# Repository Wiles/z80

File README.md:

# z80

## Purpose

Back in collage we had a real time operating systems course with targetted the Motorola 68000 CPU. It was a great course but our target platform was an emulator and not real hardware. This left a gap in my knoweldge of how things like chip selection and peripherals were handled by the hardware. Therefore I decided to design and build a barebones 8-bit computer and this is the results.

## Memory Map

| Start | End | Description |
| --- | --- | --- |
| 0x0000 | 0x7FFF | ROM |
| 0x8000 | 0x0000 | RAM |

## IO Map

| Start | End | Description |
| --- | --- | --- |
| 0x80 | 0x87 | UART |

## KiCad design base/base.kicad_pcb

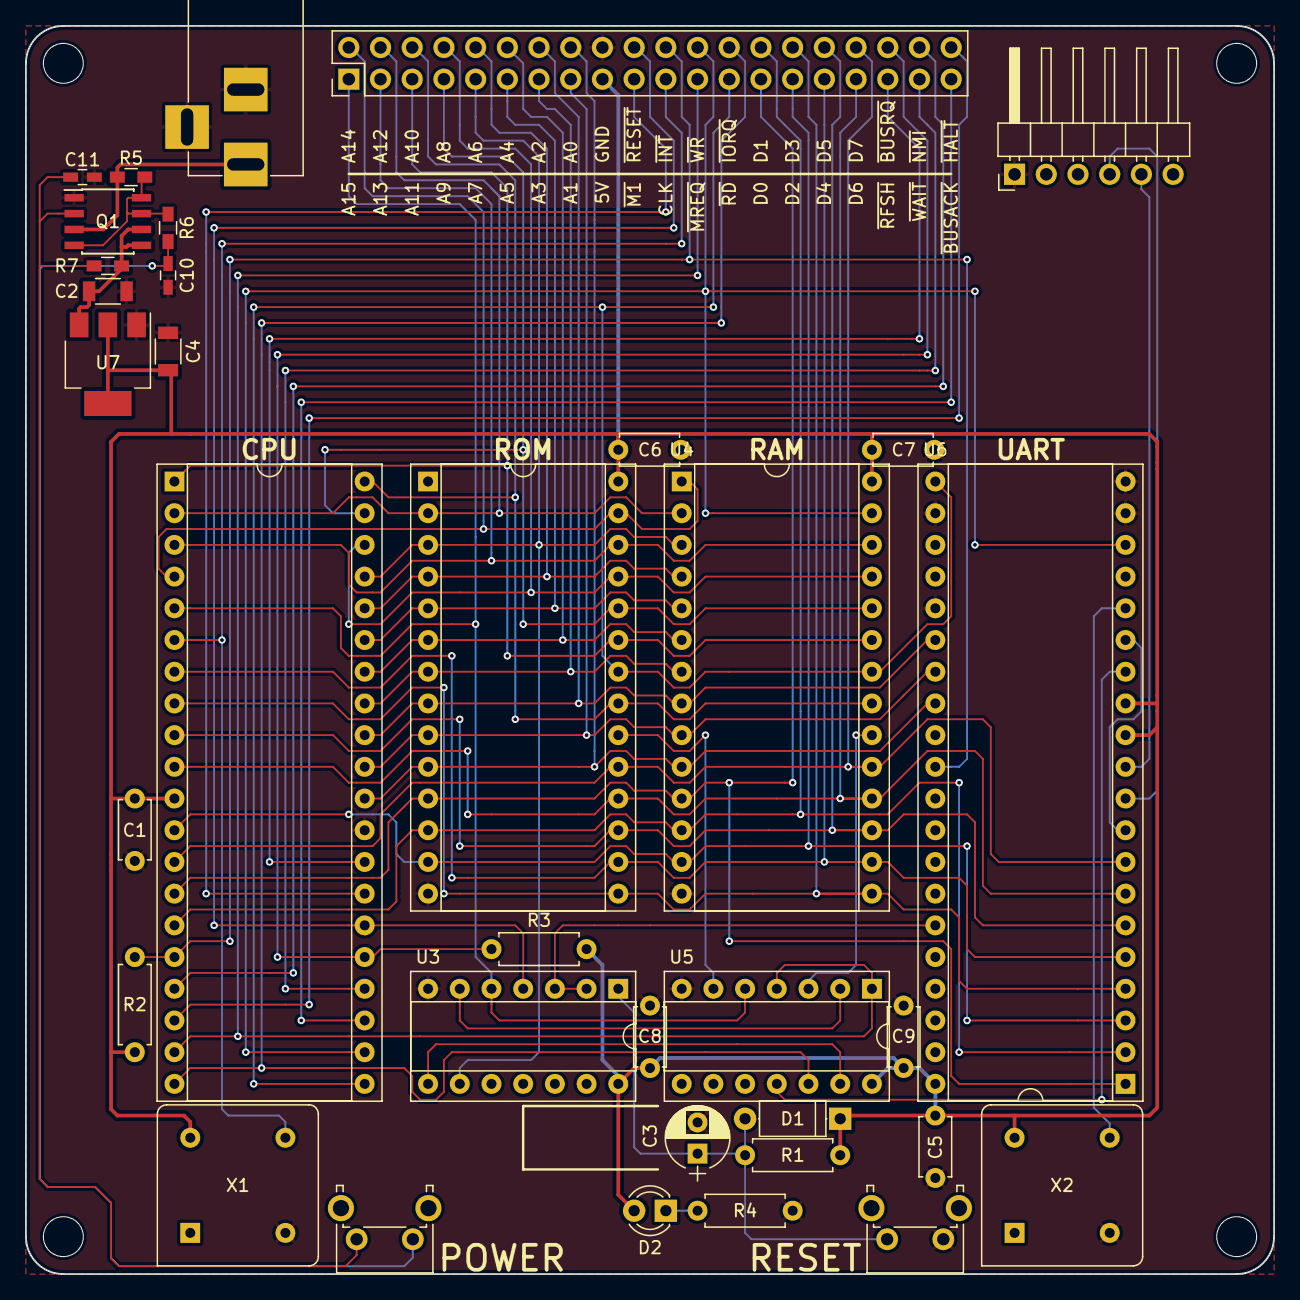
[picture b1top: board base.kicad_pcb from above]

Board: 2 copper layers, 100.0 x 100.0 mm, 35 parts (0 on the bottom side), 57 nets.

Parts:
C1, C5, C6, C7, C8, C9: .1 uF; C_Disc_D4.7mm_W2.5mm_P5.00mm
C2, C4: 10 uF; C_1206
C3: 47 uF; CP_Radial_D5.0mm_P2.50mm
C10: 1 uF; C_0603_HandSoldering
C11: .1 uF; C_0603_HandSoldering
D1: 1N4148; D_A-405_P7.62mm_Horizontal
D2: LED; LED_D3.0mm
J1: FTDI; Pin_Header_Angled_1x06_Pitch2.54mm
J2: Barrel_Jack; BARREL_JACK
J3: CONN_01X40; Pin_Header_Straight_2x20_Pitch2.54mm
Q1: IRF7309IPBF; SOIC-8_3.9x4.9mm_Pitch1.27mm
R1, R2, R3: 10k; R_Axial_DIN0207_L6.3mm_D2.5mm_P7.62mm_Horizontal
R4: 1k; R_Axial_DIN0207_L6.3mm_D2.5mm_P7.62mm_Horizontal
R5, R7: 10k; R_0603_HandSoldering
R6: 100k; R_0603_HandSoldering
SW1: RESET; SW_Tactile_SPST_Angled_PTS645Vx31-2LFS
SW2: POWER; SW_Tactile_SPST_Angled_PTS645Vx31-2LFS
U1: Z80CPU; DIP-40_W15.24mm_Socket
U2: 27C256; DIP-28_W15.24mm_Socket
U3: 7404; DIP-14_W7.62mm_Socket
U4: 55257; DIP-28_W15.24mm_Socket
U5: 7432; DIP-14_W7.62mm_Socket
U6: 16550; DIP-40_W15.24mm_Socket
U7: AP1117-50; SOT-223-3Lead_TabPin2
X1: 4 MHz; Oscillator_DIP-8
X2: 1.8432 MHz; Oscillator_DIP-8

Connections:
+5V: C1.1, C4.1, C5.1, C6.1, C7.1, C8.1, C9.1, D1.1, D2.2, J3.17, R1.1, R2.2, R3.2, U1.11, U2.28, U3.14, U4.28, U5.14, U6.12, U6.13, U6.40, U7.2, X1.8, X2.8
+VDC: J2.1, Q1.3, R5.2
+VSW: C2.1, Q1.5, Q1.6, R7.1, U7.3
/A0: J3.16, U1.30, U2.10, U4.10, U6.28
/A1: J3.15, U1.31, U2.9, U4.9, U6.27
/A2: J3.14, U1.32, U2.8, U4.8, U6.26
/A3: J3.13, U1.33, U2.7, U4.7
/A4: J3.12, U1.34, U2.6, U4.6
/A5: J3.11, U1.35, U2.5, U4.5
/A6: J3.10, U1.36, U2.4, U4.4
/A7: J3.9, U1.37, U2.3, U3.9, U4.3
/A8: J3.8, U1.38, U2.25, U4.25
/A9: J3.7, U1.39, U2.24, U4.24
/A10: J3.6, U1.40, U2.21, U4.21
/A11: J3.5, U1.1, U2.23, U4.23
/A12: J3.4, U1.2, U2.2, U4.2
/A13: J3.3, U1.3, U2.26, U4.26
/A14: J3.2, U1.4, U2.27, U4.1
/A15: J3.1, U1.5, U3.5, U5.5
/D0: J3.27, U1.14, U2.11, U4.11, U6.1
/D1: J3.28, U1.15, U2.12, U4.12, U6.2
/D2: J3.29, U1.12, U2.13, U4.13, U6.3
/D3: J3.30, U1.8, U2.15, U4.15, U6.4
/D4: J3.31, U1.7, U2.16, U4.16, U6.5
/D5: J3.32, U1.9, U2.17, U4.17, U6.6
/D6: J3.33, U1.10, U2.18, U4.18, U6.7
/D7: J3.34, U1.13, U2.19, U4.19, U6.8
BUSACK: J3.39, U1.23
BUSRQ: J3.36, R3.1, U1.25
CLOCK: J3.21, U1.6, X1.5
GND: C1.2, C2.2, C3.2, C4.2, C5.2, C6.2, C7.2, C8.2, C9.2, C10.2, C11.2, J1.1, J2.2, J2.3, J3.18, Q1.1, R4.1, SW1.1, U1.29, U2.14, U3.7, U4.14, U5.7, U6.19, U6.20, U6.22, U6.25, U7.1, X1.4, X2.4
HALT: J3.40, U1.18
INT: J3.22, R2.1, U1.16, U6.30
IORQ: J3.26, U1.20, U5.12
M1: J3.19, U1.27
MREQ: J3.23, U1.19, U5.1, U5.4
NMI: J3.38, U1.17
unnamed: C3.1, D1.2, R1.2, SW1.2, U3.1
unnamed: C10.1, R6.2, SW2.1
unnamed: C11.1, Q1.2, R7.2, SW2.2
unnamed: D2.1, R4.2
unnamed: Q1.4, Q1.7, Q1.8, R5.1, R6.1
unnamed: U3.6, U5.2
unnamed: U3.8, U5.13
unnamed: U6.9, U6.15
unnamed: U6.16, X2.5
RAM_CE: U4.20, U5.3
RD: J3.25, U1.21, U2.22, U4.22, U6.21
RESET: U3.2, U3.3, U6.35
RFSH: J3.35, U1.28
ROM_CE: U2.20, U5.6
RX: J1.5, U6.11
TX: J1.4, U6.10
UART_CE: U5.11, U6.14
WAIT: J3.37, U1.24
WR: J3.24, U1.22, U4.27, U6.18
~RESET~: J3.20, U1.26, U3.4

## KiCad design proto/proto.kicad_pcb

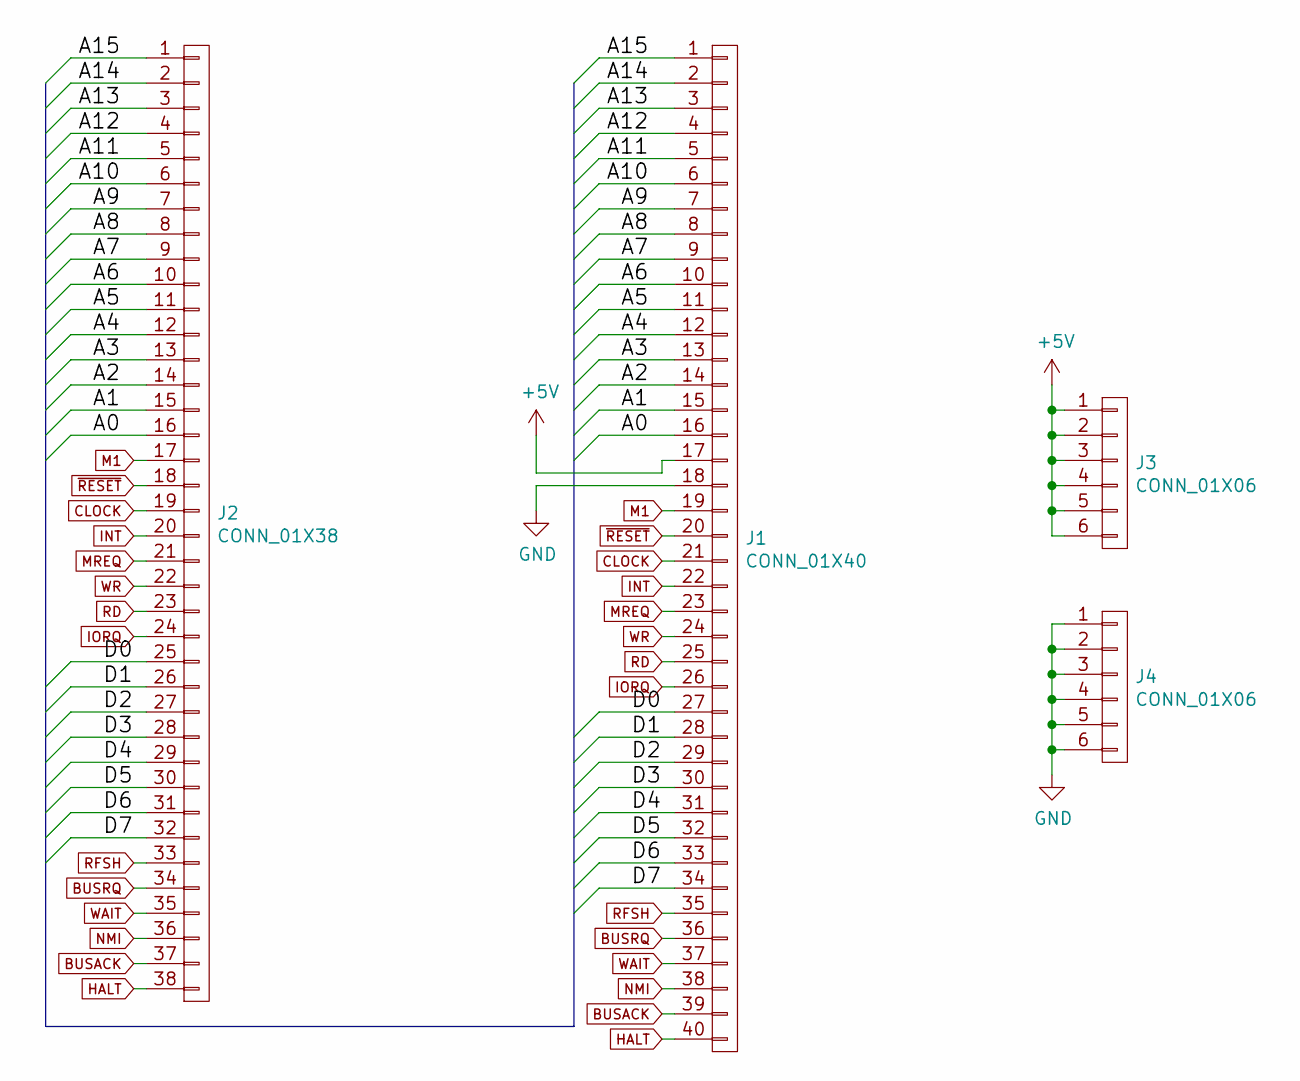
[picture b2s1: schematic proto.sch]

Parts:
J1: CONN_01X40; Pin_Header_Straight_2x20_Pitch2.54mm
J2: CONN_01X38; Pin_Header_Straight_1x38_Pitch2.54mm
J3, J4: CONN_01X06; Pin_Header_Straight_1x06_Pitch2.54mm

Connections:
+5V: J1.17, J3.1, J3.2, J3.3, J3.4, J3.5, J3.6
/A0: J1.16, J2.16
/A1: J1.15, J2.15
/A2: J1.14, J2.14
/A3: J1.13, J2.13
/A4: J1.12, J2.12
/A5: J1.11, J2.11
/A6: J1.10, J2.10
/A7: J1.9, J2.9
/A8: J1.8, J2.8
/A9: J1.7, J2.7
/A10: J1.6, J2.6
/A11: J1.5, J2.5
/A12: J1.4, J2.4
/A13: J1.3, J2.3
/A14: J1.2, J2.2
/A15: J1.1, J2.1
/D0: J1.27, J2.25
/D1: J1.28, J2.26
/D2: J1.29, J2.27
/D3: J1.30, J2.28
/D4: J1.31, J2.29
/D5: J1.32, J2.30
/D6: J1.33, J2.31
/D7: J1.34, J2.32
BUSACK: J1.39, J2.37
BUSRQ: J1.36, J2.34
CLOCK: J1.21, J2.19
GND: J1.18, J4.1, J4.2, J4.3, J4.4, J4.5, J4.6
HALT: J1.40, J2.38
INT: J1.22, J2.20
IORQ: J1.26, J2.24
M1: J1.19, J2.17
MREQ: J1.23, J2.21
NMI: J1.38, J2.36
RD: J1.25, J2.23
RFSH: J1.35, J2.33
WAIT: J1.37, J2.35
WR: J1.24, J2.22
~RESET~: J1.20, J2.18

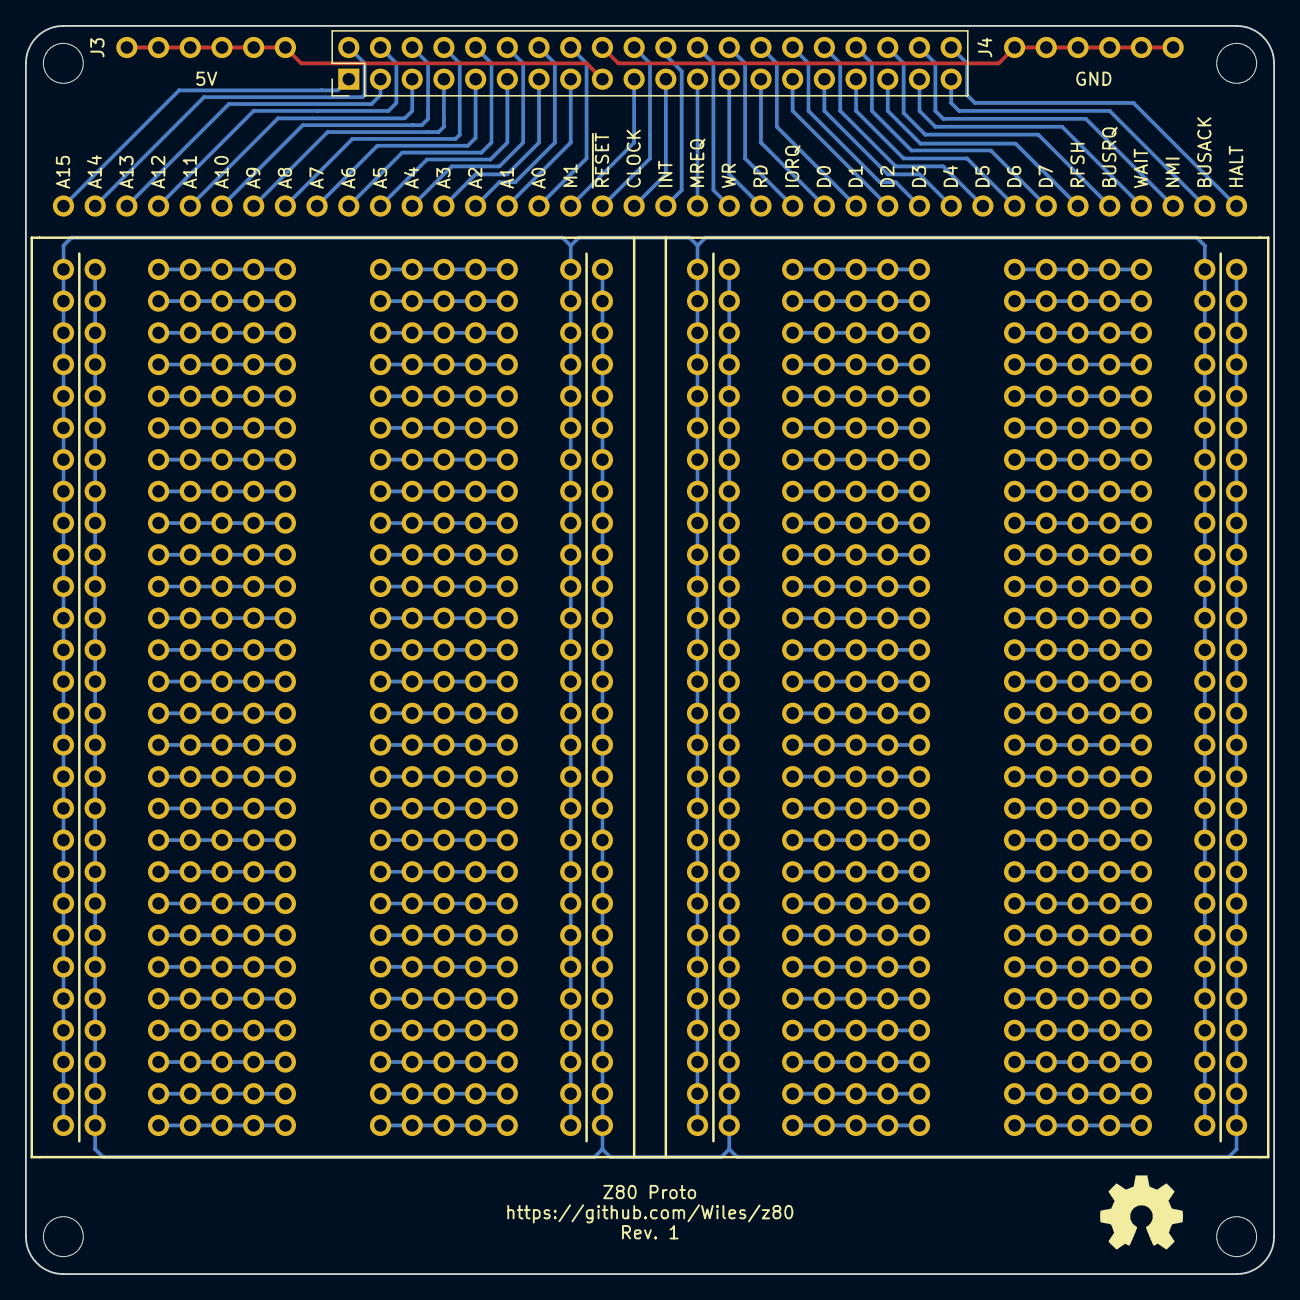
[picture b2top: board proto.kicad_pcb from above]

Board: 2 copper layers, 100.0 x 100.0 mm, 4 parts (0 on the bottom side), 40 nets.

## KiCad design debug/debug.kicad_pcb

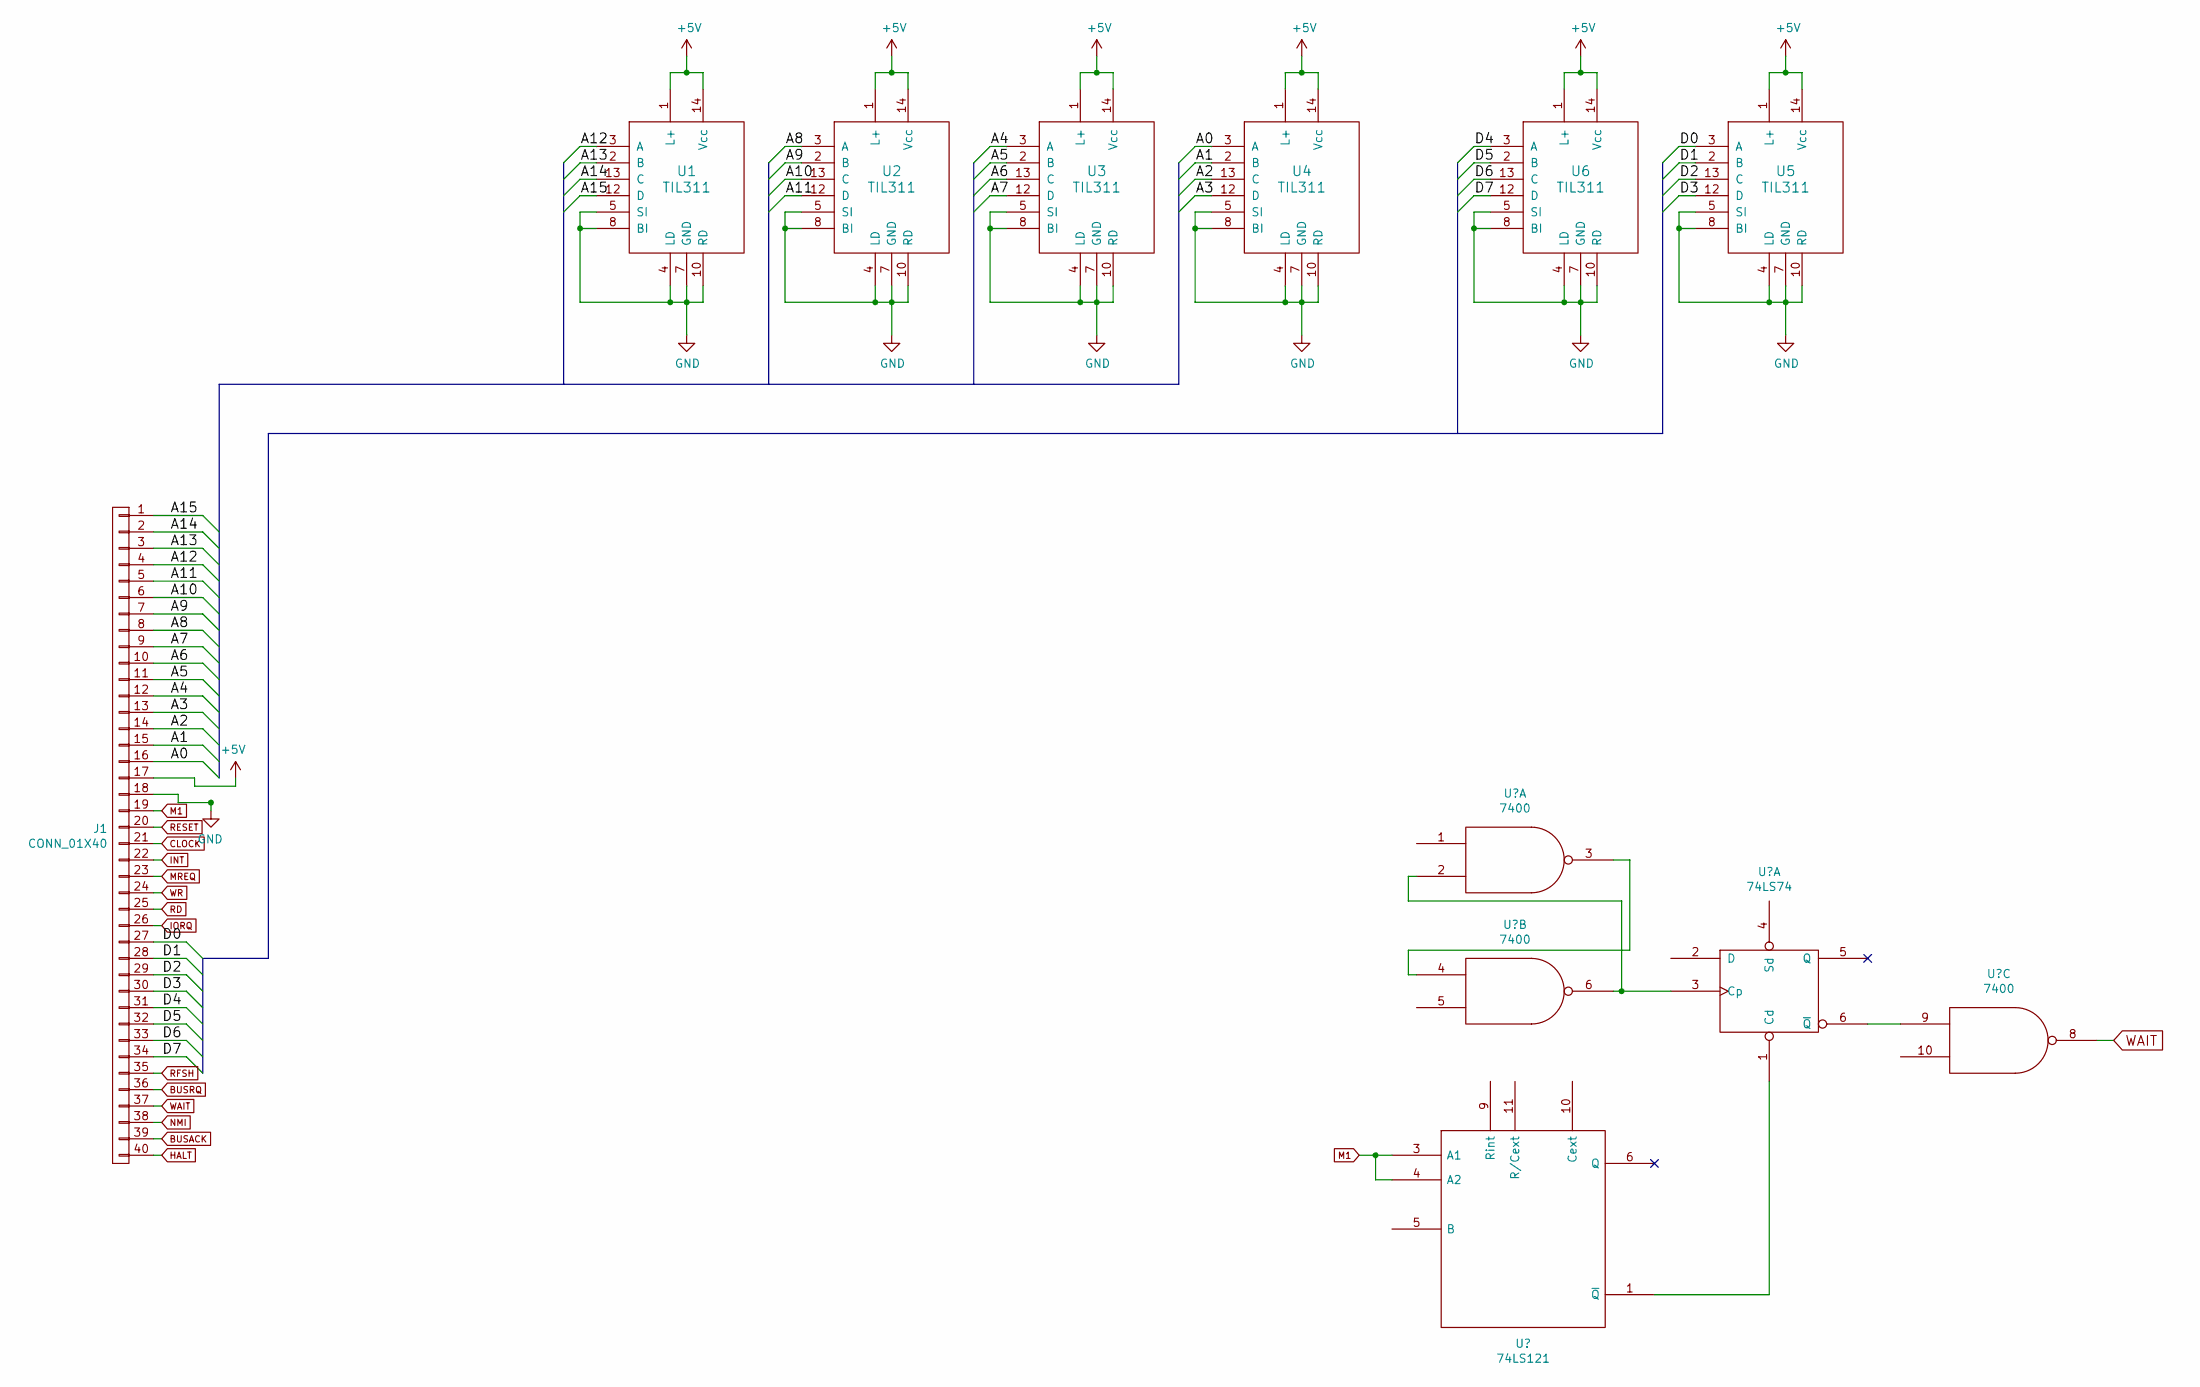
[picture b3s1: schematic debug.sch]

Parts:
J1: CONN_01X40; Pin_Header_Straight_2x20_Pitch2.54mm
U1, U2, U3, U4, U5, U6: TIL311; DIP-14_W7.62mm_Socket

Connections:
+5V: J1.17, U1.1 (L+), U1.14 (Vcc), U2.1 (L+), U2.14 (Vcc), U3.1 (L+), U3.14 (Vcc), U4.1 (L+), U4.14 (Vcc), U5.1 (L+), U5.14 (Vcc), U6.1 (L+), U6.14 (Vcc)
/A0: J1.16, U4.3 (A)
/A1: J1.15, U4.2 (B)
/A2: J1.14, U4.13 (C)
/A3: J1.13, U4.12 (D)
/A4: J1.12, U3.3 (A)
/A5: J1.11, U3.2 (B)
/A6: J1.10, U3.13 (C)
/A7: J1.9, U3.12 (D)
/A8: J1.8, U2.3 (A)
/A9: J1.7, U2.2 (B)
/A10: J1.6, U2.13 (C)
/A11: J1.5, U2.12 (D)
/A12: J1.4, U1.3 (A)
/A13: J1.3, U1.2 (B)
/A14: J1.2, U1.13 (C)
/A15: J1.1, U1.12 (D)
/D0: J1.27, U5.3 (A)
/D1: J1.28, U5.2 (B)
/D2: J1.29, U5.13 (C)
/D3: J1.30, U5.12 (D)
/D4: J1.31, U6.3 (A)
/D5: J1.32, U6.2 (B)
/D6: J1.33, U6.13 (C)
/D7: J1.34, U6.12 (D)
BUSACK: J1.39
BUSRQ: J1.36
CLOCK: J1.21
GND: J1.18, U1.4 (LD), U1.5 (SI), U1.7 (GND), U1.8 (BI), U1.10 (RD), U2.4 (LD), U2.5 (SI), U2.7 (GND), U2.8 (BI), U2.10 (RD), U3.4 (LD), U3.5 (SI), U3.7 (GND), U3.8 (BI), U3.10 (RD), U4.4 (LD), U4.5 (SI), U4.7 (GND), U4.8 (BI), U4.10 (RD), U5.4 (LD), U5.5 (SI), U5.7 (GND), U5.8 (BI), U5.10 (RD), U6.4 (LD), U6.5 (SI), U6.7 (GND), U6.8 (BI), U6.10 (RD)
HALT: J1.40
INT: J1.22
IORQ: J1.26
M1: J1.19
MREQ: J1.23
NMI: J1.38
RD: J1.25
RESET: J1.20
RFSH: J1.35
WAIT: J1.37
WR: J1.24

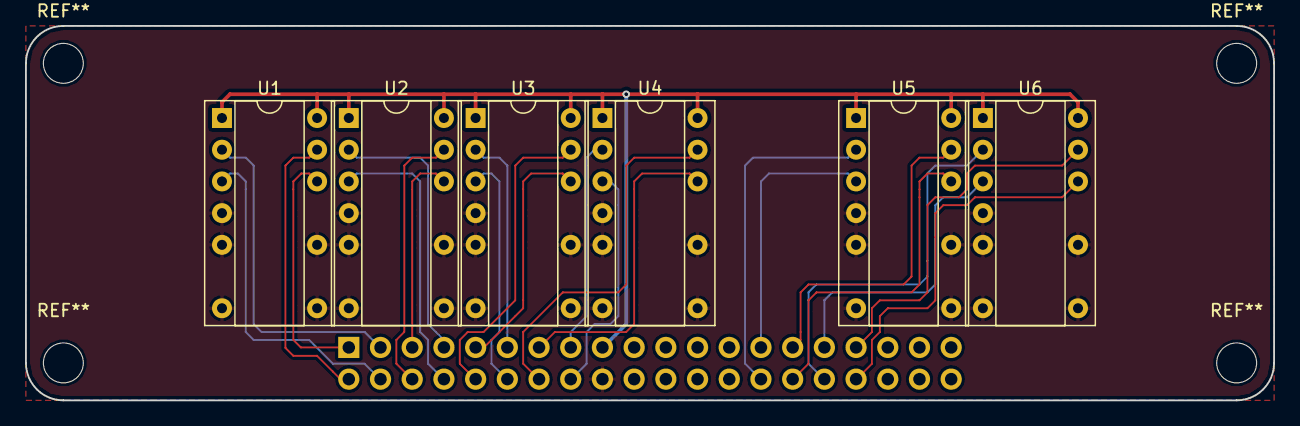
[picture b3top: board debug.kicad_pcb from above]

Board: 2 copper layers, 100.0 x 30.0 mm, 7 parts (1 on the bottom side), 26 nets.

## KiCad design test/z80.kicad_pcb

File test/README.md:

Based on the test circuit provided at http://www.z80.info/z80test0.htm.

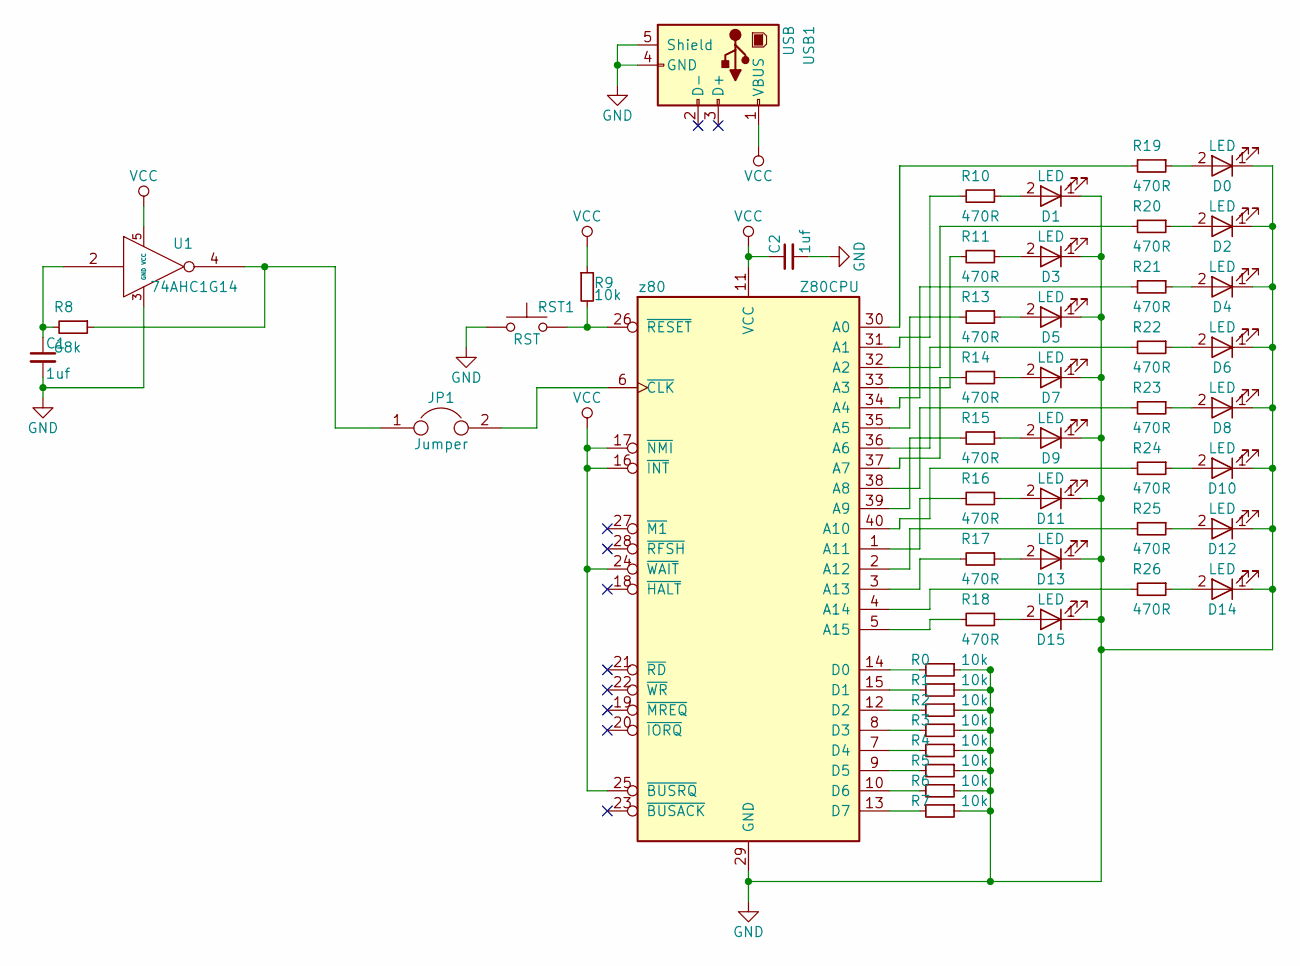
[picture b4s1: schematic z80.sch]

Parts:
C1: 1uf; C_Disc_D5.1mm_W3.2mm_P5.00mm
C2: 1uf; C_0805_HandSoldering
D0, D1, D2, D3, D4, D5, D6, D7, D8, D9, D10, D11, D12, D13, D14, D15: LED; LED_0805
JP1: Jumper; Pin_Header_Straight_1x02_Pitch2.54mm
R0, R1, R2, R3, R4, R5, R6, R7, R9: 10k; R_0805_HandSoldering
R8: 68k; R_0805_HandSoldering
R10, R11, R13, R14, R15, R16, R17, R18, R19, R20, R21, R22, R23, R24, R25, R26: 470R; R_0805_HandSoldering
RST1: RST; SW_SPST_TL3342
U1: 74AHC1G14; SOT-353_SC-70-5_Handsoldering
USB1: USB; USB_Micro-B_Molex_47346-0001
z80: Z80CPU; 40tex-Ell600

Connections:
GND: C1.2, C2.2, D0.1 (K), D1.1 (K), D2.1 (K), D3.1 (K), D4.1 (K), D5.1 (K), D6.1 (K), D7.1 (K), D8.1 (K), D9.1 (K), D10.1 (K), D11.1 (K), D12.1 (K), D13.1 (K), D14.1 (K), D15.1 (K), R0.1, R1.1, R2.1, R3.1, R4.1, R5.1, R6.1, R7.1, RST1.1, U1.3 (GND), USB1.4 (GND), USB1.5 (Shield), z80.29 (GND)
unnamed: C1.1, R8.2, U1.2
unnamed: D0.2 (A), R19.1
unnamed: D1.2 (A), R10.1
unnamed: D2.2 (A), R20.1
unnamed: D3.2 (A), R11.1
unnamed: D4.2 (A), R21.1
unnamed: D5.2 (A), R13.1
unnamed: D6.2 (A), R22.1
unnamed: D7.2 (A), R14.1
unnamed: D8.2 (A), R23.1
unnamed: D9.2 (A), R15.1
unnamed: D10.2 (A), R24.1
unnamed: D11.2 (A), R16.1
unnamed: D12.2 (A), R25.1
unnamed: D13.2 (A), R17.1
unnamed: D14.2 (A), R26.1
unnamed: D15.2 (A), R18.1
unnamed: JP1.1, R8.1, U1.4
unnamed: JP1.2, z80.6 (~CLK~)
unnamed: R0.2, z80.14 (D0)
unnamed: R1.2, z80.15 (D1)
unnamed: R2.2, z80.12 (D2)
unnamed: R3.2, z80.8 (D3)
unnamed: R4.2, z80.7 (D4)
unnamed: R5.2, z80.9 (D5)
unnamed: R6.2, z80.10 (D6)
unnamed: R7.2, z80.13 (D7)
unnamed: R9.2, RST1.2, z80.26 (~RESET~)
unnamed: R10.2, z80.31 (A1)
unnamed: R11.2, z80.33 (A3)
unnamed: R13.2, z80.35 (A5)
unnamed: R14.2, z80.37 (A7)
unnamed: R15.2, z80.39 (A9)
unnamed: R16.2, z80.1 (A11)
unnamed: R17.2, z80.3 (A13)
unnamed: R18.2, z80.5 (A15)
unnamed: R19.2, z80.30 (A0)
unnamed: R20.2, z80.32 (A2)
unnamed: R21.2, z80.34 (A4)
unnamed: R22.2, z80.36 (A6)
unnamed: R23.2, z80.38 (A8)
unnamed: R24.2, z80.40 (A10)
unnamed: R25.2, z80.2 (A12)
unnamed: R26.2, z80.4 (A14)
VCC: C2.1, R9.1, U1.5 (VCC), USB1.1 (VBUS), z80.11 (VCC), z80.16 (~INT~), z80.17 (~NMI~), z80.24 (~WAIT~), z80.25 (~BUSRQ~)

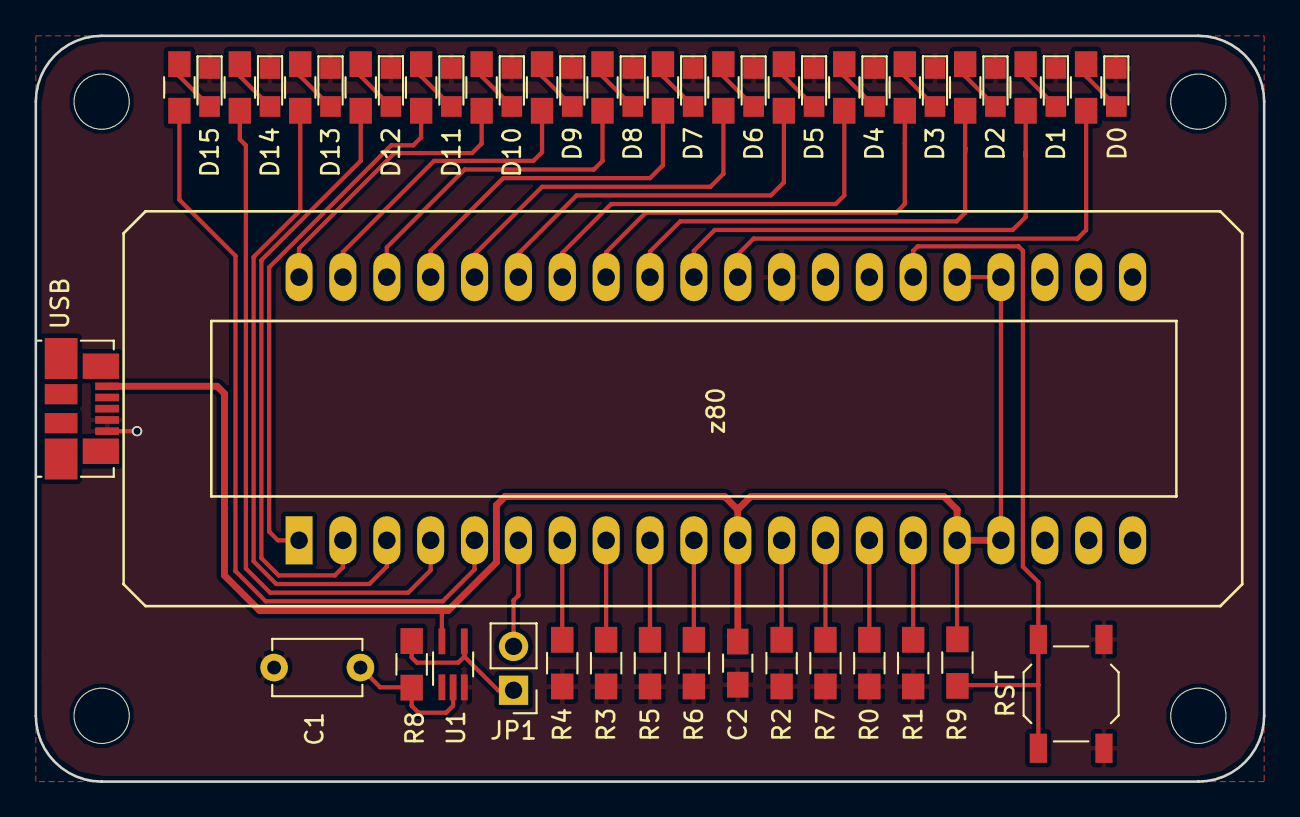
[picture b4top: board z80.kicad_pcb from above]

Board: 2 copper layers, 71.1 x 43.2 mm, 49 parts (0 on the bottom side), 46 nets.

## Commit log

2017-06-18 Revision 1 of z80 CPU test PCB
2017-06-18 Ignore gerber files
2017-06-29 Test board revision 2
    - Replaced quad NAND gate with single NOT gate
    - Broke out remaining address lines to LEDs
2017-06-29 Increase VCC track width
2017-06-29 Moved reset button label
2017-06-29 Renumber data pulldowns and address LEDs to match bits
2017-07-02 Added jumper on clock signal and replaced C1 with THT footprint.
2017-07-12 Replaced clock charge cap footprint with ceramic cap
2017-07-13 Start of base board design
2017-07-17 Layout work
2017-07-17 Replaced SMD passives with THT
2017-08-07 Further layout work
2017-10-29 Added SVG exports of current schematics
2017-10-29 Added RC2014 header to schematic
2017-10-30 Started layout of RC2014 header
2017-11-05 Finished board layout
2017-11-05 Changed FTDI and CLK_JMP footprint
2017-11-05 Fixed silkscreen
2017-11-05 Broke out remaining z80 pins
2017-11-05 Board layout for remaining pins
2017-11-06 Clean up traces
2017-11-06 Fixed board cutout
2017-11-06 Replaced main header with 2x20
2017-11-06 Added barrel jack
2017-11-06 Minor layout changes
2017-11-06 Added regulation to input voltage
2017-11-06 Fixed fill zones
2017-11-07 Change reset switch to right angle
2017-11-07 Moved voltage regulator
2017-11-07 Fixed capacitor sizes
2017-11-07 Readded mounting holes
2017-11-07 Redid power trace
2017-11-08 Increased size of voltage regulator
2017-11-08 Moved FTDI port
2017-11-08 Rev 1
2017-11-09 Start of debug board
2017-11-10 Display layout on debug board
2017-11-17 Fixed decoupling caps
2017-11-18 Clean up schematic and added more decoupling
2017-11-19 Cleaned up layout
2017-11-29 First revision of prototyping board
2018-02-19 Added memory map to README
2018-02-19 Fixed README table format
2018-02-19 Really fixed README tables
2018-02-19 Added pullups to busrq and int pins
2018-03-04 Added pinout to silkscreen
2018-03-04 Added power indicator light and changed FTDI footprint
2018-03-04 Added soft power button
2018-03-04 Fixed header pinout on back silkscreen
2020-01-08 Added image file
2020-01-08 Added image to README
2020-09-06 Added a short description to the readme
